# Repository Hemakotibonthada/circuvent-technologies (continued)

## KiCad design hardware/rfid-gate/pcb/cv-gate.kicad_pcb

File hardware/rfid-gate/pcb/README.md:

# RFID Gate PCB - KiCad project + fab checklist

Design source: SCHEMATIC.md (netlist) + BOM.csv. Open cv-gate.kicad_pro in KiCad, capture, lay out, export.

## Board spec
- 2-layer FR4, 1.6 mm, HASL lead-free, 2 oz copper on mains.
- >= 8 mm creepage / 6 mm clearance mains-to-LV; isolation slots.
- Size target ~ 75 x 60 mm (outdoor gate-post enclosure); 4x M3.
- Outdoor unit: conformal coat after test; glanded entries; drip loops.

## Pre-fab (DFM) checklist
- [ ] ERC/DRC clean at fab rules; mains clearances as keepout
- [ ] Wiegand D0/D1 pull-ups fitted; isolation upgrade reviewed (SCHEMATIC.md)
- [ ] Reader supply voltage settled - J3 carries 5 V, most UHF readers want 12 V
- [ ] External 10k pull-ups on IO34/IO35 (input-only, no internal pull-up)
- [ ] K1/K2 wired as dry contacts - board never carries motor current
- [ ] Test points: 5V, 3V3, GND, IO26/27, IO16/17 (Wiegand)
- [ ] UART/EN/IO0 pads for the flashing jig; fiducials

## Export for fab / assembly
- [ ] Gerbers + Excellon -> gerbers/; IPC-356 netlist
- [ ] BOM (BOM.csv) + CPL/centroid; PDF assembly + 3D STEP
- [ ] Order boards + stencil

## Bring-up (EVT)
- [ ] Rails before ESP32; flash test firmware over jig
- [ ] Wiegand-26 frames decode with correct parity strip
- [ ] Open/close pulses measure 600 ms at the gate controller terminals
- [ ] Loop detector holds the gate open with a vehicle present
- [ ] Allowlist survives a power cycle; works with the network down

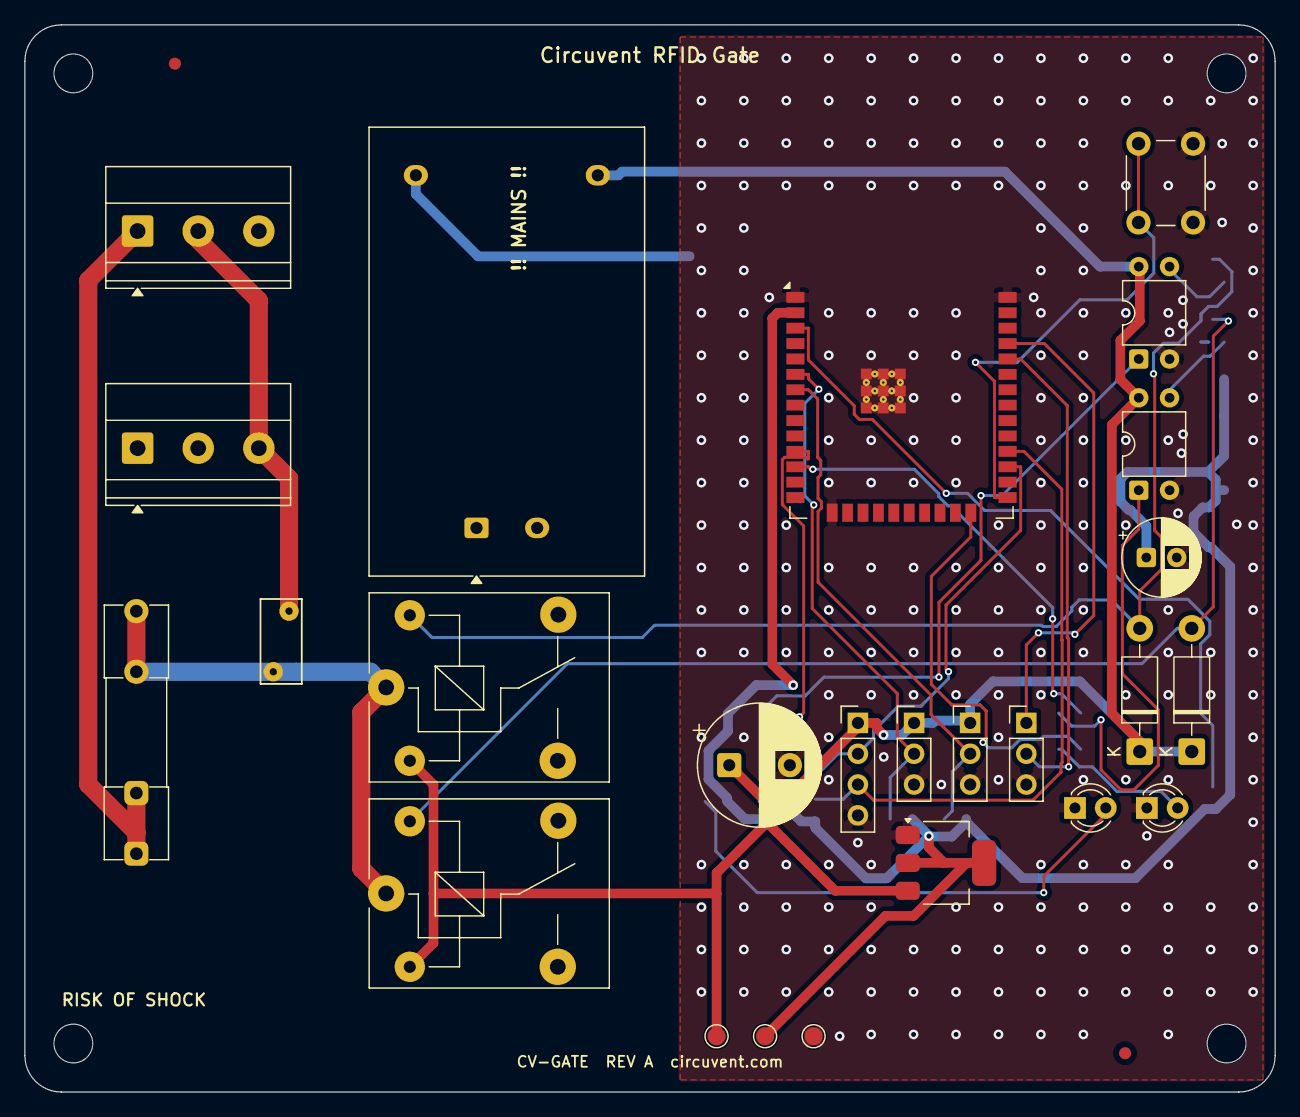
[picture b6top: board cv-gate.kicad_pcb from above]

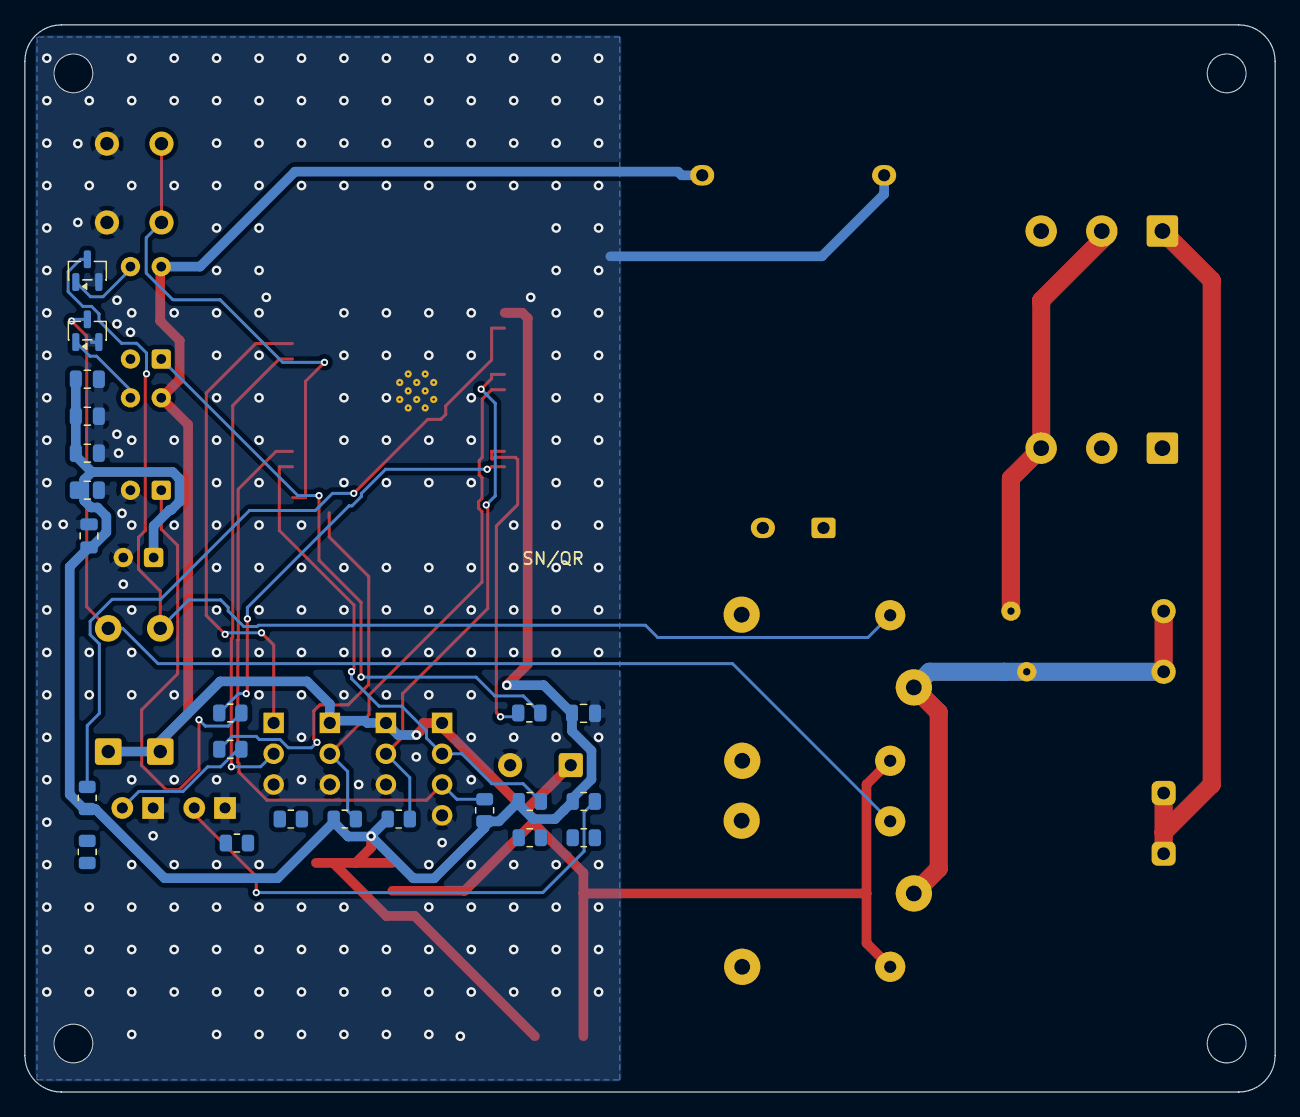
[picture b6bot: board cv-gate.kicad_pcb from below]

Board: 2 copper layers, 103.1 x 88.0 mm, 53 parts (22 on the bottom side), 27 nets.

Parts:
C1: 470uF/10V; CP_Radial_D10.0mm_P5.00mm
C2: 100uF/6.3V; CP_Radial_D6.3mm_P2.50mm
C3, C4, C5, C6, C7, C8: 100nF; C_0805_2012Metric
D1, D2: 1N4007; D_DO-41_SOD81_P10.16mm_Horizontal
F1: 2A slow-blow; Fuseholder_Clip-5x20mm_Littelfuse_111_Inline_P20.00x5.00mm_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
FID1, FID2: Fiducial; Fiducial_1mm_Mask2mm
J1: 2P 5.08mm; TerminalBlock_Phoenix_MKDS-1,5-3_1x03_P5.00mm_Horizontal
J2: 3P 5.08mm; TerminalBlock_Phoenix_MKDS-1,5-3_1x03_P5.00mm_Horizontal
J3: 4P 2.54mm; PinHeader_1x04_P2.54mm_Vertical
J4, J5: 3P 2.54mm; PinHeader_1x03_P2.54mm_Vertical
JP: 3P 2.54mm; PinHeader_1x03_P2.54mm_Vertical
K1, K2: SRD-05VDC-SL-C; Relay_SPDT_SANYOU_SRD_Series_Form_C
LED0: Green 3mm; LED_D3.0mm
LED1: Blue 3mm; LED_D3.0mm
MH1, MH2, MH3, MH4: MountingHole; MountingHole_3.2mm_M3
PS1: HLK-PM03 (5V 3W); Converter_ACDC_Hi-Link_HLK-PMxx
Q1, Q2: S8050; SOT-23
R1, R2, R3, R4, R5, R6, R7, R8, R9, R10, R11, R12, R13, R14: 10k/1k/330; R_0805_2012Metric
RV1: 7D471K; RV_Disc_D7mm_W3.4mm_P5mm
SW1: 6mm tactile; SW_PUSH_6mm_H5mm
TP1: +5V; TestPoint_Pad_D1.5mm
TP2: +3V3; TestPoint_Pad_D1.5mm
TP3: GND; TestPoint_Pad_D1.5mm
U1: ESP32-WROOM-32E (4MB); ESP32-WROOM-32E
U2: AMS1117-3.3; SOT-223-3_TabPin2
U3, U4: PC817; DIP-4_W7.62mm

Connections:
+3V3: C2.1, C3.1, C4.1, C5.1, C6.1, C7.1, C8.1, R4.1, R5.1, R6.1, R7.1, R8.1, R9.1, TP2.1, U1.2, U2.2
+5V: C1.1, D1.1, D2.1, J3.1, J4.1, J5.1, K1.2, K2.2, PS1.4, TP1.1, U2.3, U3.4, U4.4
AC_L: F1.1, J1.1
AC_L_FUSED: F1.2, K1.1, K2.1, PS1.1, RV1.1
AC_N: J1.2, J2.3, PS1.2, RV1.2
BTN_PIN: SW1.1, U1.25
CLOSE_RELAY: R2.1, U1.12
CLOSE_RELAY_COIL: D2.2, K2.5, Q2.3
CLOSE_RELAY_DRV: Q2.1, U4.3
CLOSE_RELAY_OPT: R2.2, U4.1
CLOSE_RELAY_SW: J2.2, K2.3
EN: R4.2, U1.3
GND: C1.2, C2.2, C3.2, C4.2, C5.2, C6.2, C7.2, C8.2, J3.4, J4.3, J5.3, JP.3, LED0.1, LED1.1, PS1.3, Q1.2, Q2.2, SW1.2, TP3.1, U1.1, U1.15, U1.38, U1.39, U2.1, U3.2, U4.2
LED0_A: LED0.2, R5.2
LED_PIN: R3.1, U1.24
LED_PIN_A: LED1.2, R3.2
LOOP_DETECT: J5.2, R9.2, U1.7
OPEN_LIMIT: J4.2, R8.2, U1.6
OPEN_RELAY: R1.1, U1.11
OPEN_RELAY_COIL: D1.2, K1.5, Q1.3
OPEN_RELAY_DRV: Q1.1, U3.3
OPEN_RELAY_OPT: R1.2, U3.1
OPEN_RELAY_SW: J2.1, K1.3
UART_RX: JP.2, U1.34
UART_TX: JP.1, U1.35
WIEGAND_D0: J3.2, R6.2, U1.27
WIEGAND_D1: J3.3, R7.2, U1.28

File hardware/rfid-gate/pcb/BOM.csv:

Ref,Qty,Value/Part,Package,Description,Notes
U1,1,ESP32-WROOM-32E (4MB),SMD module,Wi-Fi/BLE MCU module,Main controller
PS1,1,HLK-PM03 (5V 3W),SIP,230VAC -> 5VDC isolated PSU,2 relay coils + logic
U2,1,AMS1117-3.3,SOT-223,5V -> 3.3V LDO,MCU rail
U3,1,PC817,DIP-4,Opto-isolator,Open drive
U4,1,PC817,DIP-4,Opto-isolator,Close drive
Q1-Q2,2,S8050,SOT-23,NPN relay drivers,
D1-D2,2,1N4007,DO-41,Flyback diodes,Across each coil
K1-K2,2,SRD-05VDC-SL-C,THT relay,5V SPDT 10A,Momentary open / close
RV1,1,7D471K,disc,MOV 470V,Mains surge clamp
F1,1,2A slow-blow,5x20 holder,Mains fuse,
LED0,1,Green 3mm,THT,Power/online,
LED1,1,Blue 3mm,THT,Barrier open,IO2
SW1,1,6mm tactile,THT,Manual toggle / BOOT,IO0
J1,1,2P 5.08mm,terminal,Mains input L/N,
J2,1,3P 5.08mm,terminal,Gate controller open / close / common,Dry contacts
J3,1,4P 2.54mm,header,Wiegand reader 5V/D0/D1/GND,Long outdoor run
J4,1,3P 2.54mm,header,Gate-open limit switch,OPEN_LIMIT
J5,1,3P 2.54mm,header,Loop detector / IR beam,Vehicle present
JP,1,3P 2.54mm,header,UART (TX/RX/GND),Factory flashing
R1-R14,14,10k/1k/330,0805,Pull-ups/base/LED resistors,
C1,1,470uF/10V,electrolytic,5V bulk,
C2,1,100uF/6.3V,electrolytic,3.3V rail,
C3-C8,6,100nF,0805,Decoupling,
PCB,1,2-layer FR4 1.6mm,-,Main board,>=8mm mains-LV creepage; 2oz Cu
ENC,1,ABS IP65 (UL94 V-0),-,Outdoor gate-post enclosure,Glanded cable entries
